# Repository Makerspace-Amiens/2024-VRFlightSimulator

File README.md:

# Simulateur de Vol

Template pour la création d'un repo type projet pour le MakerSpace. Doc gérée via le thème [Just-The-Docs](https://just-the-docs.com) en vanilla.

## Bienvenue sur Notre Projet

Ce repository est le cœur de notre projet. Ici, vous trouverez toutes les ressources nécessaires pour comprendre, utiliser et contribuer à notre projet.

### Contenu du Repository

- **Documentation :** Toutes les documentations techniques et guides d'utilisation sont disponibles dans le dossier `docs`. Voir le site de doc associé. 
- **project :** Toutes les sources de notre projet.

### Comment Utiliser ce Repository ?

- Pour commencer, consultez la documentation dans le dossier `docs`.
- Si vous souhaitez contribuer au projet, veuillez lire nos directives de contribution.

## Contribution

Nous accueillons et apprécions toute contribution. Si vous souhaitez contribuer, veuillez consulter notre guide de contribution pour connaître nos attentes et notre processus.

## Contact

Si vous avez des questions ou des suggestions, n'hésitez pas à nous contacter.

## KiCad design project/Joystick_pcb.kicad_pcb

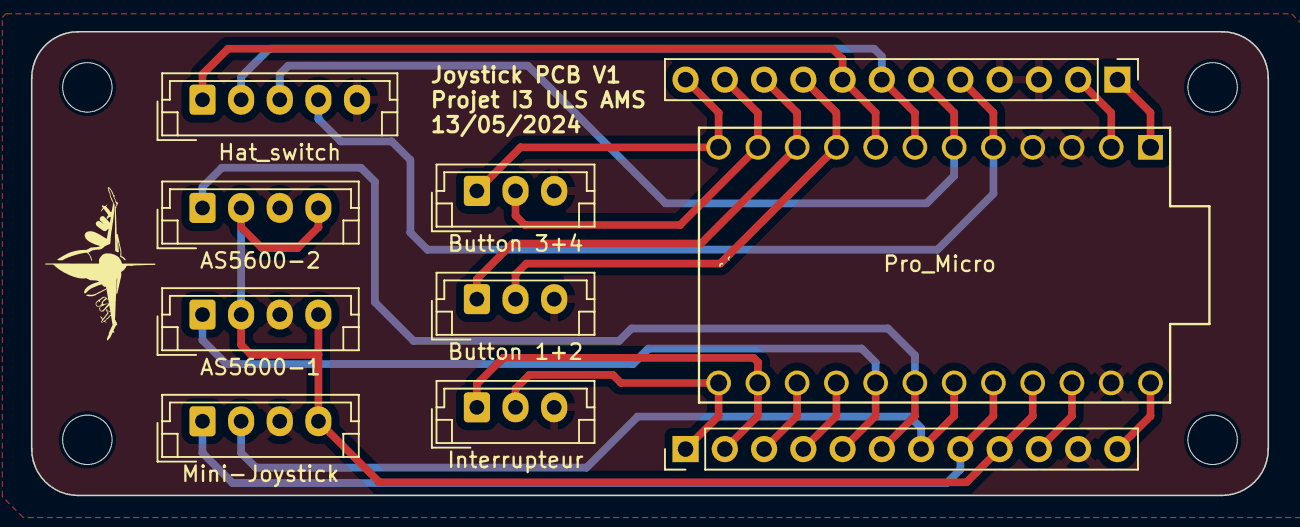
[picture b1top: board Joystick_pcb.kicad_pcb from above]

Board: 2 copper layers, 80.0 x 30.0 mm, 14 parts (0 on the bottom side), 22 nets.

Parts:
H1, H2, H3, H4: MountingHole; MountingHole_3.2mm_M3
J1: AS5600-1; JST_EH_B4B-EH-A_1x04_P2.50mm_Vertical
J2: AS5600-2; JST_EH_B4B-EH-A_1x04_P2.50mm_Vertical
J3: Mini-Joystick; JST_EH_B4B-EH-A_1x04_P2.50mm_Vertical
J4: Hat_switch; JST_EH_B5B-EH-A_1x05_P2.50mm_Vertical
J5: Button 1+2; JST_EH_B3B-EH-A_1x03_P2.50mm_Vertical
J6: Button 3+4; JST_EH_B3B-EH-A_1x03_P2.50mm_Vertical
J7: Interrupteur; JST_EH_B3B-EH-A_1x03_P2.50mm_Vertical
J8, J9: Conn_01x12_Pin; PinHeader_1x12_P2.54mm_Vertical
U1: ProMicro

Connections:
2: J4.4, J8.5, U1.5 (SDA)
3: J4.3, J8.6, U1.6 (SCL)
4: J4.2, J8.7, U1.7 (D4)
5: J4.1, J8.8, U1.8 (C6)
6: J5.2, J8.9, U1.9 (D7)
7: J5.1, J8.10, U1.10 (E6)
8: J6.2, J8.11, U1.11 (B4)
9: J6.1, J8.12, U1.12 (B5)
10: J7.2, J9.1, U1.13 (B6)
11: J7.1, J9.2, U1.14 (B2)
+5V: J1.2, J1.4, J2.2, J2.4, J3.4, J9.9, U1.21 (VCC)
A0: J1.1, J9.5, U1.17 (F7)
A1: J2.1, J9.6, U1.18 (F6)
A2: J3.2, J9.7, U1.19 (F5)
A3: J3.1, J9.8, U1.20 (F4)
GND: J1.3, J2.3, J3.3, J4.5, J5.3, J6.3, J7.3, J8.3, J8.4, J9.11, U1.3 (GND), U1.4 (GND), U1.23 (GND)
unnamed: J8.1, U1.1 (TX)
unnamed: J8.2, U1.2 (RX)
unnamed: J9.3, U1.15 (B3)
unnamed: J9.4, U1.16 (B1)
unnamed: J9.10, U1.22 (RST)
unnamed: J9.12, U1.24 (RAW)

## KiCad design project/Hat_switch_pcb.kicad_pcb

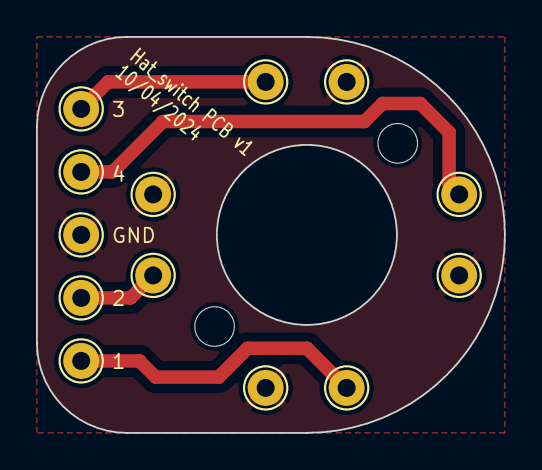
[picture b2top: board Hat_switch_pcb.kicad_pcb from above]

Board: 2 copper layers, 26.0 x 22.0 mm, 15 parts (0 on the bottom side), 5 nets.

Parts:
H1, H2: m2; MountingHole_2.2mm_M2
TP1, TP2, TP3, TP4, TP5, TP6, TP7, TP8, TP9, TP10, TP11, TP12, TP13: TestPoint_THTPad_D2.0mm_Drill1.0mm

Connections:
GND: TP1.1, TP6.1, TP8.1, TP10.1, TP12.1
unnamed: TP2.1, TP7.1
unnamed: TP4.1, TP9.1
unnamed: TP3.1, TP11.1
unnamed: TP5.1, TP13.1

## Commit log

2024-01-31 Update index.md
    Add title
2024-01-31 Add title
2024-02-21 ajout code snipet
2024-02-21 ajout pareil
2024-03-14 pareil
2024-04-04 site_3D
2024-04-05 site
2024-04-19 siteee
2024-05-14 site_simu
2024-05-24 site_projet_I3
2024-05-26 site_simulateur
2024-05-26 site_projet
2024-06-11 mise en forme
2024-06-11 Améliorations
2024-06-11 correction
2024-06-11 Corrections
2024-06-12 Création de la section conception et prototypage
2024-06-12 test
2024-06-12 ajout
2024-06-13 ajout 3D cmd
2024-06-13 Ajout STEP
2024-06-13 Ajout PCB + code
